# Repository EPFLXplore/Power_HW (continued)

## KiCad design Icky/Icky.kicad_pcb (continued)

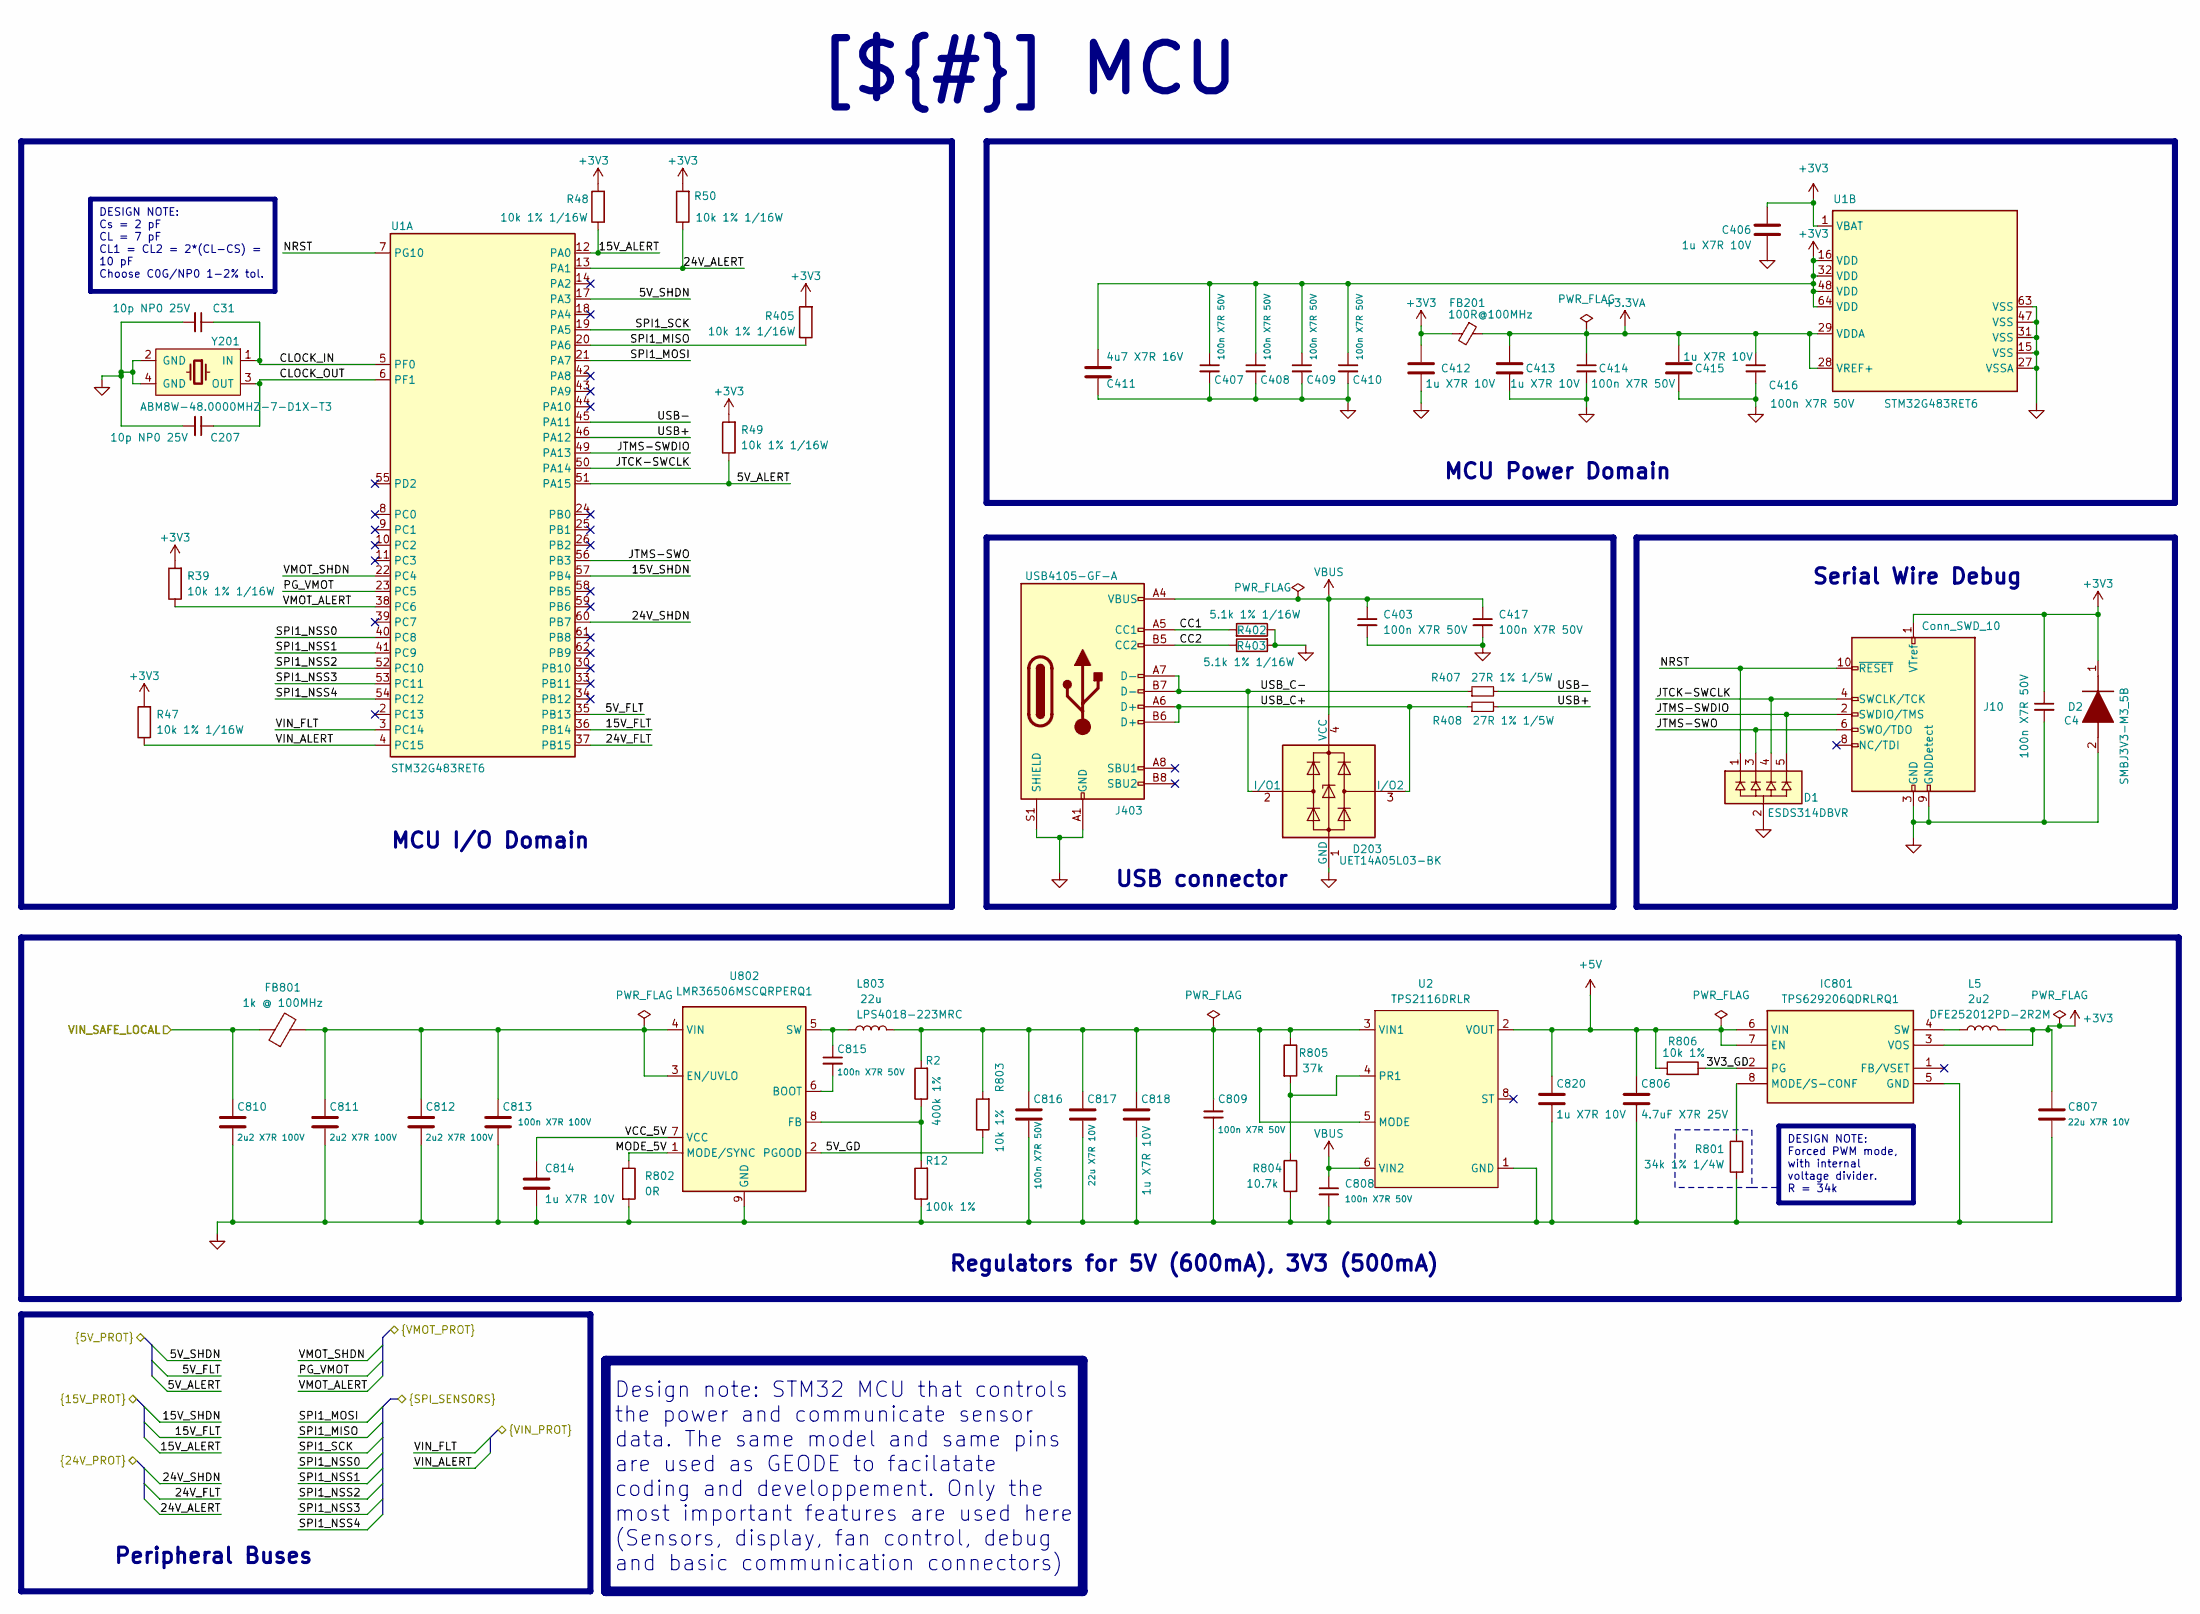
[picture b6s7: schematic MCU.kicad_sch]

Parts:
C4, C403, C407, C408, C409, C410, C414, C416, C417, C808, C809, C815, C816: 100n X7R 50V; C_0603_1608Metric; Manufacturer Part Number GCM155R71H104KE02J
C31, C207: 10p NP0 25V; C_0603_1608Metric
C406, C412, C413, C415, C814, C818, C820: 1u X7R 10V; C_0603_1608Metric; Manufacturer Part Number GRM155Z71A105KE01J
C411: 4u7 X7R 16V; C_0603_1608Metric; Manufacturer Part Number GRM188Z71C475KE21J
C806: 4.7uF X7R 25V; C_0603_1608Metric
C807, C817: 22u X7R 10V; C_0603_1608Metric; Manufacturer Part Number GRM21BZ71A226ME15L
C810, C811, C812: 2u2 X7R 100V; C_0603_1608Metric; Manufacturer Part Number CGA4J1X7R2A225K125AC
C813: 100n X7R 100V; C_0603_1608Metric; Manufacturer Part Number HMK107B7104KAHT
D1: ESDS314DBVR; SOT95P280X145-5N; Mouser Part Number 595-ESDS314DBVR
D2: SMBJ3V3-M3_5B; DIONM5436X244N; Mouser Part Number 78-SMBJ3V3-M35B
D203: UET14A05L03-BK; SOT-143
FB201: 100R@100MHz; L_0603_1608Metric; Digikey ref 490-13260-1-ND
FB801: 1k @ 100MHz; R_0805_2012Metric; Manufacturer Part Number 742792096
IC801: TPS629206QDRLRQ1; SOTFL50P160X60-8N; Mouser Part Number 595-TPS629206QDRLRQ1
J10: Conn_SWD_10; PinHeader_2x05_P1.27mm_Horizontal; Manufacturer Part Number FTSH10501FDRAK; Mouser ref 200-FTSH10501FDRAK
J403: USB4105-GF-A; USB_C_Receptacle_GCT_USB4105-xx-A_16P_TopMnt_Horizontal
L5: 2u2; L_1008_2520Metric; Manufacturer Part Number DFE252012PD-2R2M
L803: 22u; L_Coilcraft_LPS4018; Manufacturer Part Number LPS4018-223MRC
R2: 400k 1%; R_0603_1608Metric
R12: 100k 1%; R_0603_1608Metric
R39, R47, R48, R49, R50, R405: 10k 1% 1/16W; R_0603_1608Metric
R402, R403: 5.1k 1% 1/16W; R_0603_1608Metric
R407, R408: 27R 1% 1/5W; R_0603_1608Metric; Manufacturer Part Number RCS0402100RFKED
R801: 34k 1% 1/4W; R_0603_1608Metric
R802: 0R; R_0603_1608Metric; Manufacturer Part Number ERJ-2GE0R00X
R803, R806: 10k 1%; R_0603_1608Metric; Manufacturer Part Number RT0402FRE0710KL
R804: 10.7k; R_0603_1608Metric; Manufacturer Part Number ERJ-2GE0R00X
R805: 37k; R_0603_1608Metric; Manufacturer Part Number ERJ-2GE0R00X
U1: STM32G483RET6; LQFP-64_10x10mm_P0.5mm
U2: TPS2116DRLR; SOTFL50P160X60-8N; Digikey ref 296-TPS2116DRLRCT-ND
U802: LMR36506MSCQRPERQ1; LMR36506MSC5RPERQ1; Manufacturer Part Number LMR36506MSCQRPERQ1
Y201: ABM8W-48.0000MHZ-7-D1X-T3; ABM8W480000MHZ6D1XT3; Digikey ref ABM8W-48.0000MHZ-7-D1X-T3

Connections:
+3.3VA: C413.1, C414.1, C415.1, C416.1, FB201.1, U1.28 (VREF+), U1.29 (VDDA)
+3V3: C4.1, C406.1, C407.1, C408.1, C409.1, C410.1, C411.1, C412.1, C807.1, D2.1 (K), FB201.2, IC801.3 (VOS), J10.1 (VTref), L5.2, R39.2, R47.2, R48.2, R49.2, R50.2, R405.2, U1.1 (VBAT), U1.16 (VDD), U1.32 (VDD), U1.48 (VDD), U1.64 (VDD); also elsewhere on the board
+5V: C806.2, C820.1, IC801.6 (VIN), IC801.7 (EN), R806.2, U2.2 (VOUT), U2.7 (VOUT)
/Project Architecture/MCU & Local Power/3V3_GD: IC801.2 (PG), R806.1
/Project Architecture/MCU & Local Power/5V_ALERT: R49.1, U1.51 (PA15); also elsewhere on the board
/Project Architecture/MCU & Local Power/5V_FLT: U1.35 (PB13); also elsewhere on the board
/Project Architecture/MCU & Local Power/5V_GD: R803.1, U802.2 (PGOOD)
/Project Architecture/MCU & Local Power/5V_SHDN: U1.17 (PA3); also elsewhere on the board
/Project Architecture/MCU & Local Power/15V_ALERT: R48.1, U1.12 (PA0); also elsewhere on the board
/Project Architecture/MCU & Local Power/15V_FLT: U1.36 (PB14); also elsewhere on the board
/Project Architecture/MCU & Local Power/15V_SHDN: U1.57 (PB4); also elsewhere on the board
/Project Architecture/MCU & Local Power/24V_ALERT: R50.1, U1.13 (PA1); also elsewhere on the board
/Project Architecture/MCU & Local Power/24V_FLT: U1.37 (PB15); also elsewhere on the board
/Project Architecture/MCU & Local Power/24V_SHDN: U1.60 (PB7); also elsewhere on the board
/Project Architecture/MCU & Local Power/CC1: J403.A5 (CC1), R402.2
/Project Architecture/MCU & Local Power/CC2: J403.B5 (CC2), R403.1
/Project Architecture/MCU & Local Power/CLOCK_IN: C31.1, U1.5 (PF0), Y201.1 (IN)
/Project Architecture/MCU & Local Power/CLOCK_OUT: C207.1, U1.6 (PF1), Y201.3 (OUT)
/Project Architecture/MCU & Local Power/JTCK-SWCLK: D1.4, J10.4 (SWCLK/TCK), U1.50 (PA14)
/Project Architecture/MCU & Local Power/JTMS-SWDIO: D1.5, J10.2 (SWDIO/TMS), U1.49 (PA13)
/Project Architecture/MCU & Local Power/JTMS-SWO: D1.3, J10.6 (SWO/TDO), U1.56 (PB3)
/Project Architecture/MCU & Local Power/MODE_5V: R802.1, U802.1 (MODE/SYNC)
/Project Architecture/MCU & Local Power/NRST: D1.1, J10.10 (~RESET), U1.7 (PG10)
/Project Architecture/MCU & Local Power/PG_VMOT: U1.23 (PC5); also elsewhere on the board
/Project Architecture/MCU & Local Power/SPI1_MISO: R405.1, U1.20 (PA6); also elsewhere on the board
/Project Architecture/MCU & Local Power/SPI1_MOSI: U1.21 (PA7); also elsewhere on the board
/Project Architecture/MCU & Local Power/SPI1_NSS0: U1.40 (PC8); also elsewhere on the board
/Project Architecture/MCU & Local Power/SPI1_NSS1: U1.41 (PC9); also elsewhere on the board
/Project Architecture/MCU & Local Power/SPI1_NSS2: U1.52 (PC10); also elsewhere on the board
/Project Architecture/MCU & Local Power/SPI1_NSS3: U1.53 (PC11); also elsewhere on the board
/Project Architecture/MCU & Local Power/SPI1_NSS4: U1.54 (PC12); also elsewhere on the board
/Project Architecture/MCU & Local Power/SPI1_SCK: U1.19 (PA5); also elsewhere on the board
/Project Architecture/MCU & Local Power/USB+: R408.2, U1.46 (PA12)
/Project Architecture/MCU & Local Power/USB-: R407.2, U1.45 (PA11)
/Project Architecture/MCU & Local Power/USB_C+: D203.3 (I/O2), J403.A6 (D+), J403.B6 (D+), R408.1
/Project Architecture/MCU & Local Power/USB_C-: D203.2 (I/O1), J403.A7 (D-), J403.B7 (D-), R407.1
/Project Architecture/MCU & Local Power/VCC_5V: C814.1, U802.7 (VCC)
/Project Architecture/MCU & Local Power/VIN_ALERT: R47.1, U1.4 (PC15); also elsewhere on the board
/Project Architecture/MCU & Local Power/VIN_FLT: U1.3 (PC14); also elsewhere on the board
/Project Architecture/MCU & Local Power/VMOT_ALERT: R39.1, U1.38 (PC6); also elsewhere on the board
/Project Architecture/MCU & Local Power/VMOT_SHDN: U1.22 (PC4); also elsewhere on the board
unnamed: IC801.8 (MODE/S-CONF), R801.1
unnamed: IC801.4 (SW), L5.1
unnamed: C809.1, C816.1, C817.1, C818.1, L803.2, R2.2, R803.2, R805.1, U2.3 (VIN1), U2.5 (MODE)
unnamed: R804.1, R805.2, U2.4 (PR1)
unnamed: C815.2, U802.6 (BOOT)
unnamed: C811.1, C812.1, C813.1, FB801.2, U802.3 (EN/UVLO), U802.4 (VIN)
unnamed: R2.1, R12.2, U802.8 (FB)
unnamed: C815.1, L803.1, U802.5 (SW)
VBUS: C403.1, C417.1, C808.1, D203.4 (VCC), J403.A4 (VBUS), J403.A9 (VBUS), J403.B4 (VBUS), J403.B9 (VBUS), U2.6 (VIN2)

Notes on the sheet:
Design note: STM32 MCU that controls the power and communicate sensor data. The same model and same pins are used as GEODE to facilatate coding and developpement. Only the most important features are used here (Sensors, display, fan control, debug and basic communication connectors)
Serial Wire Debug
[${#}] ${TITLE}
Regulators for 5V (600mA), 3V3 (500mA)
DESIGN NOTE: Cs = 2 pF CL = 7 pF CL1 = CL2 = 2*(CL-CS) = 10 pF Choose C0G/NP0 1-2% tol.
MCU Power Domain
DESIGN NOTE: Forced PWM mode, with internal voltage divider. R = 34k
MCU I/O Domain
Peripheral Buses
USB connector

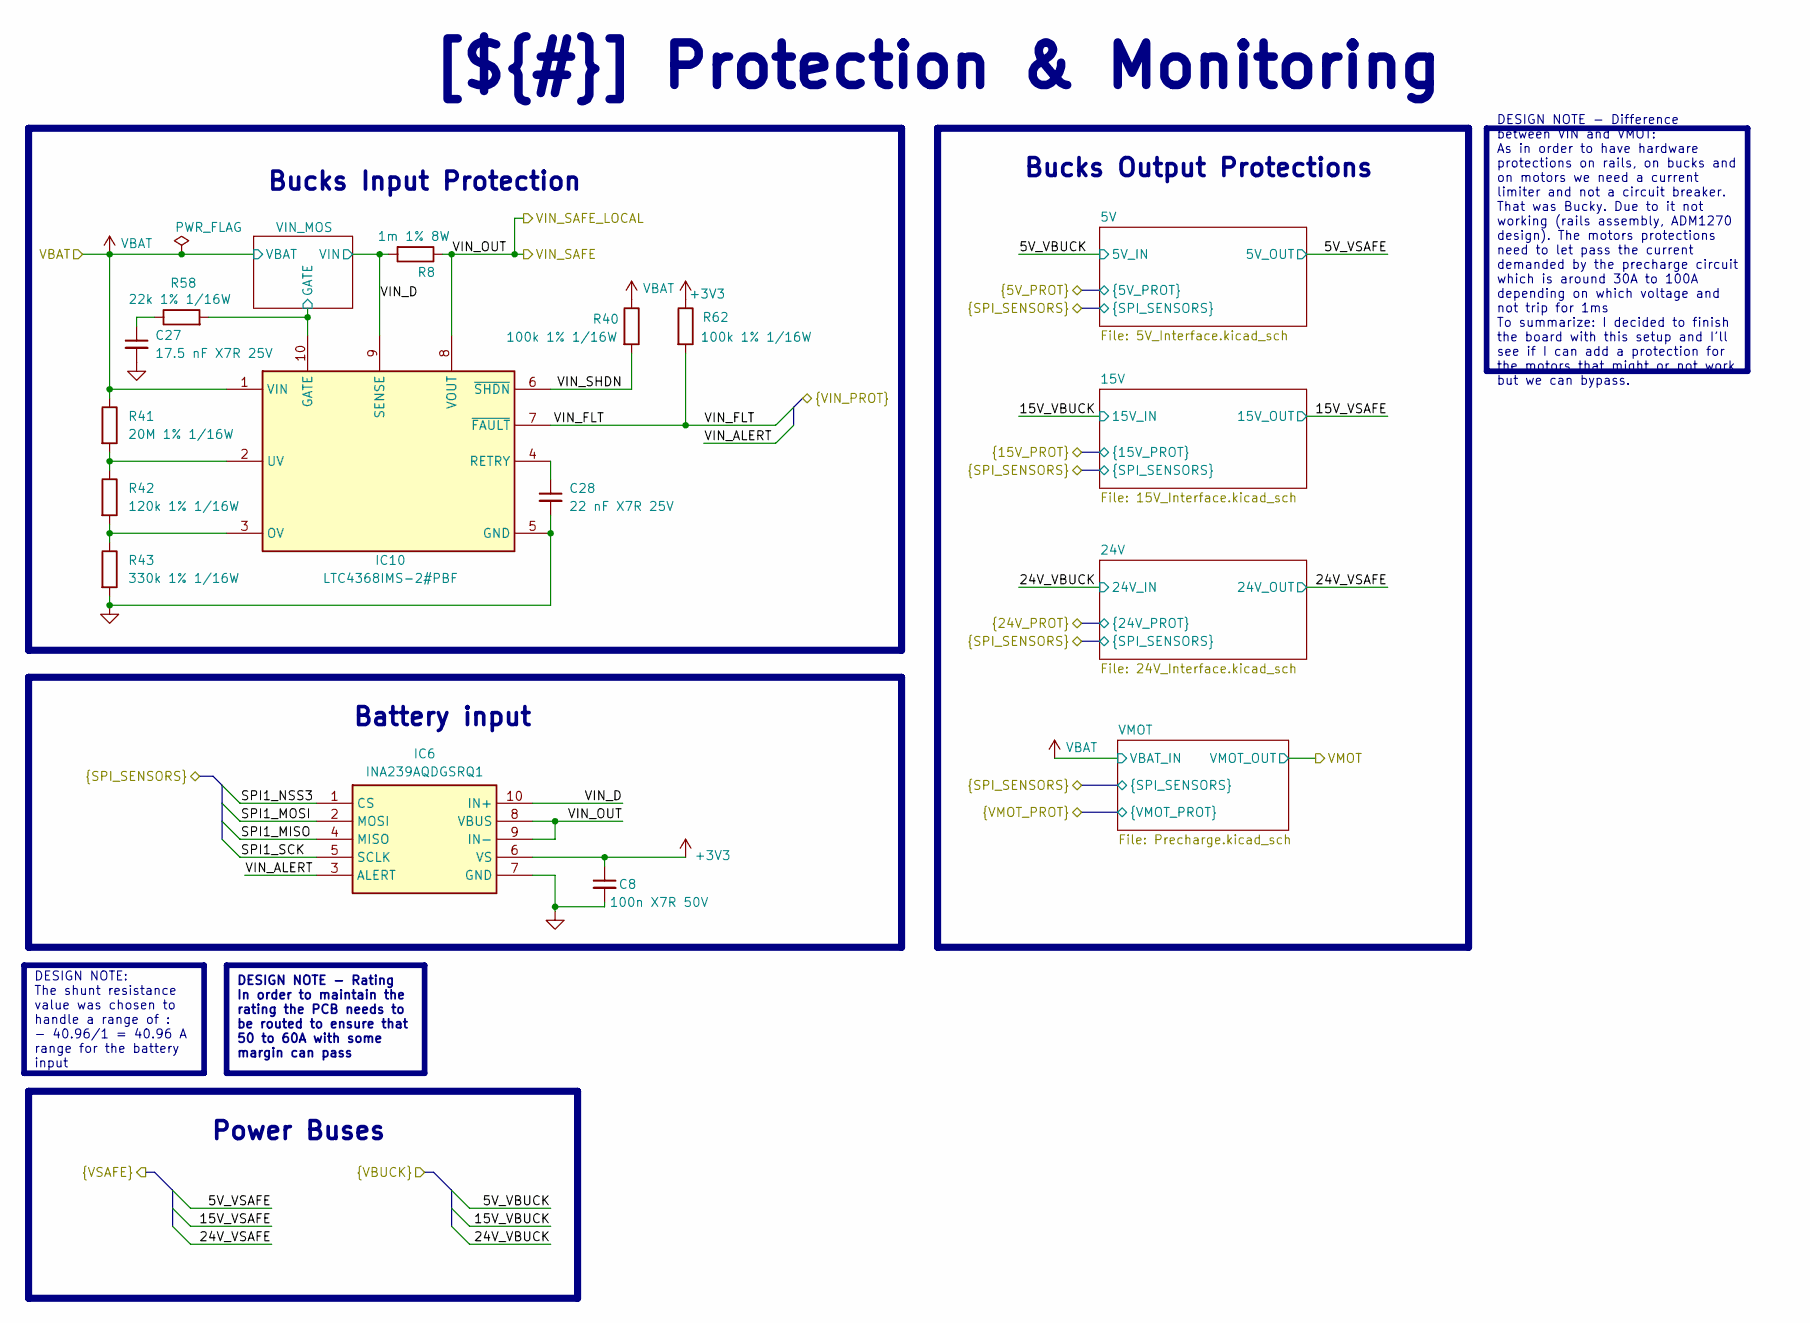
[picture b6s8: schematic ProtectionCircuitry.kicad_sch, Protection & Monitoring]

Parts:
C8: 100n X7R 50V; C_0603_1608Metric; Manufacturer Part Number GCM155R71H104KE02J
C27: 17.5 nF X7R 25V; C_0603_1608Metric
C28: 22 nF X7R 25V; C_0603_1608Metric
IC6: INA239AQDGSRQ1; SOP50P490X110-10N; Mouser Part Number 595-INA239AQDGSRQ1
IC10: LTC4368IMS-2#PBF; SOP50P490X110-10N; Mouser Part Number 584-LTC4368IMS2PBF
R8: 1m 1% 8W; WSL39211L000JEA
R40, R62: 100k 1% 1/16W; R_0603_1608Metric
R41: 20M 1% 1/16W; R_0603_1608Metric
R42: 120k 1% 1/16W; R_0603_1608Metric
R43: 330k 1% 1/16W; R_0603_1608Metric
R58: 22k 1% 1/16W; R_0603_1608Metric

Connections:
+3V3: C8.1, IC6.6 (VS), R62.1; also elsewhere on the board
/Project Architecture/MCU & Local Power/SPI1_MISO: IC6.4 (MISO); also elsewhere on the board
/Project Architecture/MCU & Local Power/SPI1_MOSI: IC6.2 (MOSI); also elsewhere on the board
/Project Architecture/MCU & Local Power/SPI1_NSS3: IC6.1 (CS); also elsewhere on the board
/Project Architecture/MCU & Local Power/SPI1_SCK: IC6.5 (SCLK); also elsewhere on the board
/Project Architecture/MCU & Local Power/VIN_ALERT: IC6.3 (ALERT); also elsewhere on the board
/Project Architecture/MCU & Local Power/VIN_FLT: IC10.7 (~FAULT), R62.2; also elsewhere on the board
/Project Architecture/Protection & Monitoring/VIN_D: IC6.10 (IN+), IC10.9 (SENSE), R8.2; also elsewhere on the board
/Project Architecture/Protection & Monitoring/VIN_MOS/GATE: IC10.10 (GATE), R58.2; also elsewhere on the board
/Project Architecture/Protection & Monitoring/VIN_SHDN: IC10.6 (~SHDN), R40.2
unnamed: C27.1, R58.1
unnamed: IC10.3 (OV), R42.2, R43.1
unnamed: C28.1, IC10.4 (RETRY)
unnamed: IC10.2 (UV), R41.2, R42.1
VBAT: IC10.1 (VIN), R40.1, R41.1; also elsewhere on the board

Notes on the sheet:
Bucks Input Protection
Battery input
Power Buses
Bucks Output Protections
DESIGN NOTE: The shunt resistance value was chosen to handle a range of : - 40.96/1 = 40.96 A range for the battery input
DESIGN NOTE - Difference between VIN and VMOT: As in order to have hardware protections on rails, on bucks and on motors we need a current limiter and not a circuit breaker. That was Bucky. Due to it not working (rails assembly, ADM1270 design). The motors protections need to let pass the current d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
DESIGN NOTE - Rating In order to maintain the rating the PCB needs to be routed to ensure that 50 to 60A with some margin can pass
[${#}] ${TITLE}

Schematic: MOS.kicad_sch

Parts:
C1, C5: 6.8 nF X7R 50V
R13, R14, R15, R16: 10 1% 1/16W
U3, U4, U14, U15: SQJQ112E-T1_GE3; DPAK_2E-T1_GE3_VIS

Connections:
/Project Architecture/Protection & Monitoring/VIN_D: U14.5 (D), U15.5 (D); also elsewhere on the board
/Project Architecture/Protection & Monitoring/VIN_MOS/GATE: C1.2, C5.2, R13.2, R14.2, R15.1, R16.1; also elsewhere on the board
unnamed: C1.1, U3.2 (S), U3.3 (S), U3.4 (S), U14.2 (S), U14.3 (S), U14.4 (S)
unnamed: C5.1, U4.2 (S), U4.3 (S), U4.4 (S), U15.2 (S), U15.3 (S), U15.4 (S)
unnamed: R15.2, U3.1 (G)
unnamed: R16.2, U4.1 (G)
unnamed: R13.1, U14.1 (G)
unnamed: R14.1, U15.1 (G)
VBAT: U3.5 (D), U4.5 (D); also elsewhere on the board

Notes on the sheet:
DESIGN NOTE - 2 parallel pairs / temperature check 40A path 3 MOSFETs in parallel per leg back to back = 6 total 2 parallel not enough as Rds(on) total used = 2.53m x 2 / 3 = about 7mOhm path (derated to 175 which is worst case) Steady loss with 2 parallel pairs = 20^2 x 7m = 2.8W * 40°C = 112°C + 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

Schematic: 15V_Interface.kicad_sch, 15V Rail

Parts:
C2: 100n X7R 50V; C_0402_1005_DensityHigh; Manufacturer Part Number GCM155R71H104KE02J
C23: 17.5 nF X7R 25V
C24: 22 nF X7R 25V
C34: 6.8 nF X7R 50V
IC2: INA239AQDGSRQ1; SOP50P490X110-10N; Mouser Part Number 595-INA239AQDGSRQ1
IC8: LTC4368IMS-2#PBF; SOP50P490X110-10N; Mouser Part Number 584-LTC4368IMS2PBF
NT3: NetTieShuntH; NetTie-2_SMD_Pad0.2mm
NT4: NetTieShuntL; NetTie-2_SMD_Pad0.2mm
Q2: SOT233 BSS123N; SOT-23-3
R22, R23, R46: 100k 1% 1/16W
R24: 6.8M 1% 1/16W
R25: 56k 1% 1/16W
R26: 330k 1% 1/16W
R27: 22k 1% 1/16W
R28, R29: 10 1% 1/16W
R30: 4m
U9, U10: SQJQ112E-T1_GE3; DPAK_2E-T1_GE3_VIS

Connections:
+3V3: C2.1, IC2.6 (VS), R46.1; also elsewhere on the board
/Project Architecture/MCU & Local Power/15V_ALERT: IC2.3 (ALERT); also elsewhere on the board
/Project Architecture/MCU & Local Power/15V_FLT: IC8.7 (~FAULT), R46.2; also elsewhere on the board
/Project Architecture/MCU & Local Power/15V_SHDN: Q2.1 (G), R22.1; also elsewhere on the board
/Project Architecture/MCU & Local Power/SPI1_MISO: IC2.4 (MISO); also elsewhere on the board
/Project Architecture/MCU & Local Power/SPI1_MOSI: IC2.2 (MOSI); also elsewhere on the board
/Project Architecture/MCU & Local Power/SPI1_NSS1: IC2.1 (CS); also elsewhere on the board
/Project Architecture/MCU & Local Power/SPI1_SCK: IC2.5 (SCLK); also elsewhere on the board
/Project Architecture/PowerConnectors/15V_VBUCK: IC8.1 (VIN), R23.1, R24.1, U9.5 (D); also elsewhere on the board
/Project Architecture/Protection & Monitoring/15V/15V_SHDN_PIN: IC8.6 (~SHDN), Q2.3 (D), R23.2
unnamed: C23.1, R27.1
unnamed: C34.1, U9.2 (S), U9.3 (S), U9.4 (S), U10.2 (S), U10.3 (S), U10.4 (S)
unnamed: C34.2, IC8.10 (GATE), R27.2, R28.1, R29.1
unnamed: IC8.3 (OV), R25.2, R26.1
unnamed: C24.1, IC8.4 (RETRY)
unnamed: IC8.2 (UV), R24.2, R25.1
unnamed: R28.2, U9.1 (G)
unnamed: R29.2, U10.1 (G)

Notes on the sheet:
[${#}] ${TITLE}
DESIGN NOTE - Loss / temperature Pair hot resistance estimate about 16.5mOhm (worst case VGS and derated with the graph) Use Rds(on) vs Tj graph as reference Ppair = I^2 x R = 10^2 x 0.0165 = 1.65W R_jtoamb = 40°C/W => 1.65W * 40°C/W = 66°C + 55° (Poland, summer, hot metal box) = 121 °C < 175 °C
Rail Protection
DESIGN NOTE - TO COMPLETE
DESIGN NOTE - Rating In order to maintain the rating the PCB needs to be routed to ensure that 10 to 15A with some margin can pass
15V Rail Sensor

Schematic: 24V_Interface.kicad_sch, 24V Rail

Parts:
C3: 100n X7R 50V; C_0603_1608Metric; Manufacturer Part Number GCM155R71H104KE02J
C25: 17.5 nF X7R 25V; C_0603_1608Metric
C26: 22 nF X7R 25V; C_0603_1608Metric
C35: 6.8 nF X7R 50V; C_0603_1608Metric
IC3: INA239AQDGSRQ1; SOP50P490X110-10N; Mouser Part Number 595-INA239AQDGSRQ1
IC9: LTC4368IMS-2#PBF; SOP50P490X110-10N; Mouser Part Number 584-LTC4368IMS2PBF
Q3: SOT233 BSS123N; BSS123N
R1, R3, R31: 100k 1% 1/16W; R_0603_1608Metric
R32: 15M 1% 1/16W; R_0603_1608Metric
R33: 39k 1% 1/16W; R_0603_1608Metric
R34: 300k 1% 1/16W; R_0603_1608Metric
R35: 22k 1% 1/16W; R_0603_1608Metric
R36, R37: 10 1% 1/16W; R_0603_1608Metric
R38: 4m; R_2010_5025Metric
U11, U12: SQJQ112E-T1_GE3; DPAK_2E-T1_GE3_VIS

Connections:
+3V3: C3.1, IC3.6 (VS), R3.1; also elsewhere on the board
/Project Architecture/MCU & Local Power/24V_ALERT: IC3.3 (ALERT); also elsewhere on the board
/Project Architecture/MCU & Local Power/24V_FLT: IC9.7 (~FAULT), R3.2; also elsewhere on the board
/Project Architecture/MCU & Local Power/24V_SHDN: Q3.1 (G), R1.1; also elsewhere on the board
/Project Architecture/MCU & Local Power/SPI1_MISO: IC3.4 (MISO); also elsewhere on the board
/Project Architecture/MCU & Local Power/SPI1_MOSI: IC3.2 (MOSI); also elsewhere on the board
/Project Architecture/MCU & Local Power/SPI1_NSS2: IC3.1 (CS); also elsewhere on the board
/Project Architecture/MCU & Local Power/SPI1_SCK: IC3.5 (SCLK); also elsewhere on the board
/Project Architecture/PowerConnectors/24V_VBUCK: IC9.1 (VIN), R31.1, R32.1, U11.5 (D); also elsewhere on the board
/Project Architecture/Protection & Monitoring/24V/24V_D: IC3.10 (IN+), IC9.9 (SENSE), R38.2, U12.5 (D)
/Project Architecture/Protection & Monitoring/24V/24V_SHDN_PIN: IC9.6 (~SHDN), Q3.3 (D), R31.2
unnamed: C25.1, R35.1
unnamed: C35.1, U11.2 (S), U11.3 (S), U11.4 (S), U12.2 (S), U12.3 (S), U12.4 (S)
unnamed: C35.2, IC9.10 (GATE), R35.2, R36.1, R37.1
unnamed: IC9.3 (OV), R33.2, R34.1
unnamed: C26.1, IC9.4 (RETRY)
unnamed: IC9.2 (UV), R32.2, R33.1
unnamed: R36.2, U11.1 (G)
unnamed: R37.2, U12.1 (G)

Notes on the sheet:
Rail Protection
24V Rail Sensor
[${#}] ${TITLE}
DESIGN NOTE - TO COMPLETE
DESIGN NOTE - Loss / temperature Pair hot resistance estimate about 16.5mOhm (worst case VGS and derated with the graph) Use Rds(on) vs Tj graph as reference Ppair = I^2 x R = 10^2 x 0.0165 = 1.65W R_jtoamb = 40°C/W => 1.65W * 40°C/W = 66°C + 55° (Poland, summer, hot metal box) = 121 °C < 175 °C
DESIGN NOTE - Rating In order to maintain the rating the PCB needs to be routed to ensure that 10 to 15A with some margin can pass

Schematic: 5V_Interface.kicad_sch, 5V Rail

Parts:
C15: 100n X7R 50V; C_0402_1005_DensityHigh; Manufacturer Part Number GCM155R71H104KE02J
C18: 17.5 nF X7R 25V
C19: 22 nF X7R 25V
C32: 6.8 nF X7R 50V
IC4: LTC4368IMS-2#PBF; SOP50P490X110-10N; Mouser Part Number 584-LTC4368IMS2PBF
IC7: INA239AQDGSRQ1; SOP50P490X110-10N; Mouser Part Number 595-INA239AQDGSRQ1
NT9: NetTieShuntH; NetTie-2_SMD_Pad0.2mm
NT10: NetTieShuntL; NetTie-2_SMD_Pad0.2mm
Q1102: SOT233 BSS123N; SOT-23-3
R4: 470k 1% 1/16W
R5: 4m
R6: 150k 1% 1/16W
R7: 4.75M 1% 1/16W
R9: 22k 1% 1/16W
R10, R11, R52: 100k 1% 1/16W
R18, R19: 10 1% 1/16W
U5, U6: SQJQ112E-T1_GE3; DPAK_2E-T1_GE3_VIS

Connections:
+3V3: C15.1, IC7.6 (VS), R52.1; also elsewhere on the board
/Project Architecture/MCU & Local Power/5V_ALERT: IC7.3 (ALERT); also elsewhere on the board
/Project Architecture/MCU & Local Power/5V_FLT: IC4.7 (~FAULT), R52.2; also elsewhere on the board
/Project Architecture/MCU & Local Power/5V_SHDN: Q1102.1 (G), R11.1; also elsewhere on the board
/Project Architecture/MCU & Local Power/SPI1_MISO: IC7.4 (MISO); also elsewhere on the board
/Project Architecture/MCU & Local Power/SPI1_MOSI: IC7.2 (MOSI); also elsewhere on the board
/Project Architecture/MCU & Local Power/SPI1_NSS0: IC7.1 (CS); also elsewhere on the board
/Project Architecture/MCU & Local Power/SPI1_SCK: IC7.5 (SCLK); also elsewhere on the board
/Project Architecture/PowerConnectors/5V_VBUCK: IC4.1 (VIN), R7.1, R10.1, U5.5 (D); also elsewhere on the board
/Project Architecture/Protection & Monitoring/5V/5V_SHDN_PIN: IC4.6 (~SHDN), Q1102.3 (D), R10.2; also elsewhere on the board
unnamed: C18.1, R9.1
unnamed: C32.1, U5.2 (S), U5.3 (S), U5.4 (S), U6.2 (S), U6.3 (S), U6.4 (S)
unnamed: C32.2, IC4.10 (GATE), R9.2, R18.1, R19.1
unnamed: IC4.3 (OV), R4.1, R6.2
unnamed: C19.1, IC4.4 (RETRY)
unnamed: IC4.2 (UV), R6.1, R7.2
unnamed: R18.2, U5.1 (G)
unnamed: R19.2, U6.1 (G)

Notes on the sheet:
DESIGN NOTE - UV / OV / control R1 + R2 = Vos(UV) / Iuv => Using Vos(UV) = 3mV and Iuv = 10nA => R1 + R2 = 300k R3 = (Vos(UV) / Iuv) x ((UVth - 0.5) / 0.5) => R3 = 300k x ((UVth - 0.5) / 0.5) R1 = (300k + R3) x 0.5 / OVth => R2 = 300k - R1 UV about 4.3V + OV about 5.6V => R1 = 470k, R2 = 150k, R3 =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
DESIGN NOTE - Gate charge / timing Use 8V gate charge estimate, not 10V form table below Qmos pair about 300nC + Qcgate = 18nF x 8V = 144nC => Qtotal about 444nC => Ton about Q / I = 444nC / 35uA = 12.5ms typ Fast pull-down region about 60mA typ => Toff about 9us typ region
Rail Protection
DESIGN NOTE - Loss / temperature Pair hot resistance estimate about 16.5mOhm (worst case VGS and derated with the graph) Use Rds(on) vs Tj graph as reference Ppair = I^2 x R = 10^2 x 0.0165 = 1.65W R_jtoamb = 40°C/W => 1.65W * 40°C/W = 66°C + 55° (Poland, summer, hot metal box) = 121 °C < 175 °C
DESIGN NOTE - Rating In order to maintain the rating the PCB needs to be routed to ensure that 10 to 15A with some margin can pass
5V Rail Sensor
[${#}] ${TITLE}
DESIGN NOTE - Startup / inrush Cout budget = about 500uF 200uF local + downstream margin Target cap charging current = about 1A Cgate from Iinrush = Cout / Cgate x Igate(up) Using Igate(up) typ = 35uA Cgate about 18nF Ramp time = C x V / I = 500uF x 5V / 1A = 2.5ms Add LTC turn-on delay = about 32m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
DESIGN NOTE - Gate drive / current limit Vgate - Vout at 5V input = 7.2V min - 8.7V typ => good enough for 5V rail Rsense = 4 mOhm => Itrip typ = 50mV / 4mOhm = 12.5A & Itrip min = 40mV / 4mOhm = 10A & Itrip max = 60mV / 4mOhm = 15A Irev = 3mV / 4mOhm = 0.75A
DESIGN NOTE - SHUNT 4m form the other component maps to 40.96mV/4m = 10A so valid

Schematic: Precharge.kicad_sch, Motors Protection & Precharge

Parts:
C6, C22, C29: 100n X7R 50V; C_0402_1005_DensityHigh; Manufacturer Part Number GCM155R71H104KE02J
C20: 470n X7R 50V; C_0402_1005_DensityHigh; Manufacturer Part Number GCM155R71H104KE02J
IC1: LM5069MM-2_NOPB; SOP50P490X110-10N; Mouser Part Number 926-LM5069MM-2/NOPB
IC5: INA239AQDGSRQ1; SOP50P490X110-10N; Mouser Part Number 595-INA239AQDGSRQ1
NT1: NetTieShuntH; NetTie-2_SMD_Pad0.2mm
NT2: NetTieShuntL; NetTie-2_SMD_Pad0.2mm
Q1: SOT233 BSS123N; SOT-23-3
R17: 120k 1% 1/16W; R_0603_1608Metric
R20: 1m 1% 4W
R21, R56: 100k 1% 1/16W
R44, R45, R51: 10 1% 1/16W
R53, R54: 10k 1% 1/16W; R_0603_1608Metric
R55: 22k 1% 1/16W; R_0603_1608Metric
U7, U8, U17: SQJQ112E-T1_GE3; DPAK_2E-T1_GE3_VIS

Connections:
+3V3: C29.1, IC5.6 (VS), R21.1; also elsewhere on the board
/Project Architecture/MCU & Local Power/PG_VMOT: IC1.8 (PGD), R21.2; also elsewhere on the board
/Project Architecture/MCU & Local Power/SPI1_MISO: IC5.4 (MISO); also elsewhere on the board
/Project Architecture/MCU & Local Power/SPI1_MOSI: IC5.2 (MOSI); also elsewhere on the board
/Project Architecture/MCU & Local Power/SPI1_NSS4: IC5.1 (CS); also elsewhere on the board
/Project Architecture/MCU & Local Power/SPI1_SCK: IC5.5 (SCLK); also elsewhere on the board
/Project Architecture/MCU & Local Power/VMOT_ALERT: IC5.3 (ALERT); also elsewhere on the board
/Project Architecture/MCU & Local Power/VMOT_SHDN: Q1.1 (G), R56.1; also elsewhere on the board
unnamed: IC1.10 (GATE), R44.1, R45.1, R51.1
unnamed: IC1.4 (OVLO), R53.2, R54.1
unnamed: IC1.7 (PWR), R55.1
unnamed: C20.1, C22.1, IC1.6 (TIMER)
unnamed: IC1.3 (UVLO), Q1.3 (D), R17.2, R53.1
unnamed: R45.2, U7.1 (G)
unnamed: R51.2, U8.1 (G)
unnamed: R44.2, U17.1 (G)
VBAT: C6.1, IC1.2 (VIN), IC5.10 (IN+), NT1.1, NT1.2, R17.1, R20.2; also elsewhere on the board

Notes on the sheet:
Motors Protection
DESIGN NOTE - CALCULATOR Designed with the Excel calculator on Computations, refer to that document for capabilities
Motor Input Sensor
DESIGN NOTE - REASONING Separate protections for bucks and motors was chosen becuase of the fact that the precharge circuit used at xplore is based on the TPS2490 which is not that much of a technical precharge but an inrush limiter. That function is the same as the original ADM1270 on Bucky. Due t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
[${#}] ${TITLE}

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
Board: 6 copper layers, 204 parts (0 on the bottom side), 119 nets, no tracks yet.

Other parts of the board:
C30: 6.8 nF X7R 50V; C_0603_1608Metric
Q4: SOT233 BSS123N; BSS123N
R57, R59: 10 1% 1/16W; R_0603_1608Metric
U13, U16: SQJQ112E-T1_GE3; DPAK_2E-T1_GE3_VIS

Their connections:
/Project Architecture/MCU & Local Power/5V_SHDN: Q4.1 (G); also elsewhere on the board
/Project Architecture/Protection & Monitoring/5V/5V_SHDN_PIN: Q4.3 (D); also elsewhere on the board
/Project Architecture/Protection & Monitoring/VIN_D: U16.5 (D); also elsewhere on the board
/Project Architecture/Protection & Monitoring/VIN_MOS/GATE: C30.2, R57.1, R59.2; also elsewhere on the board
unnamed: C30.1, U13.2 (S), U13.3 (S), U13.4 (S), U16.2 (S), U16.3 (S), U16.4 (S)
unnamed: R57.2, U13.1 (G)
unnamed: R59.1, U16.1 (G)
VBAT: U13.5 (D); also elsewhere on the board
